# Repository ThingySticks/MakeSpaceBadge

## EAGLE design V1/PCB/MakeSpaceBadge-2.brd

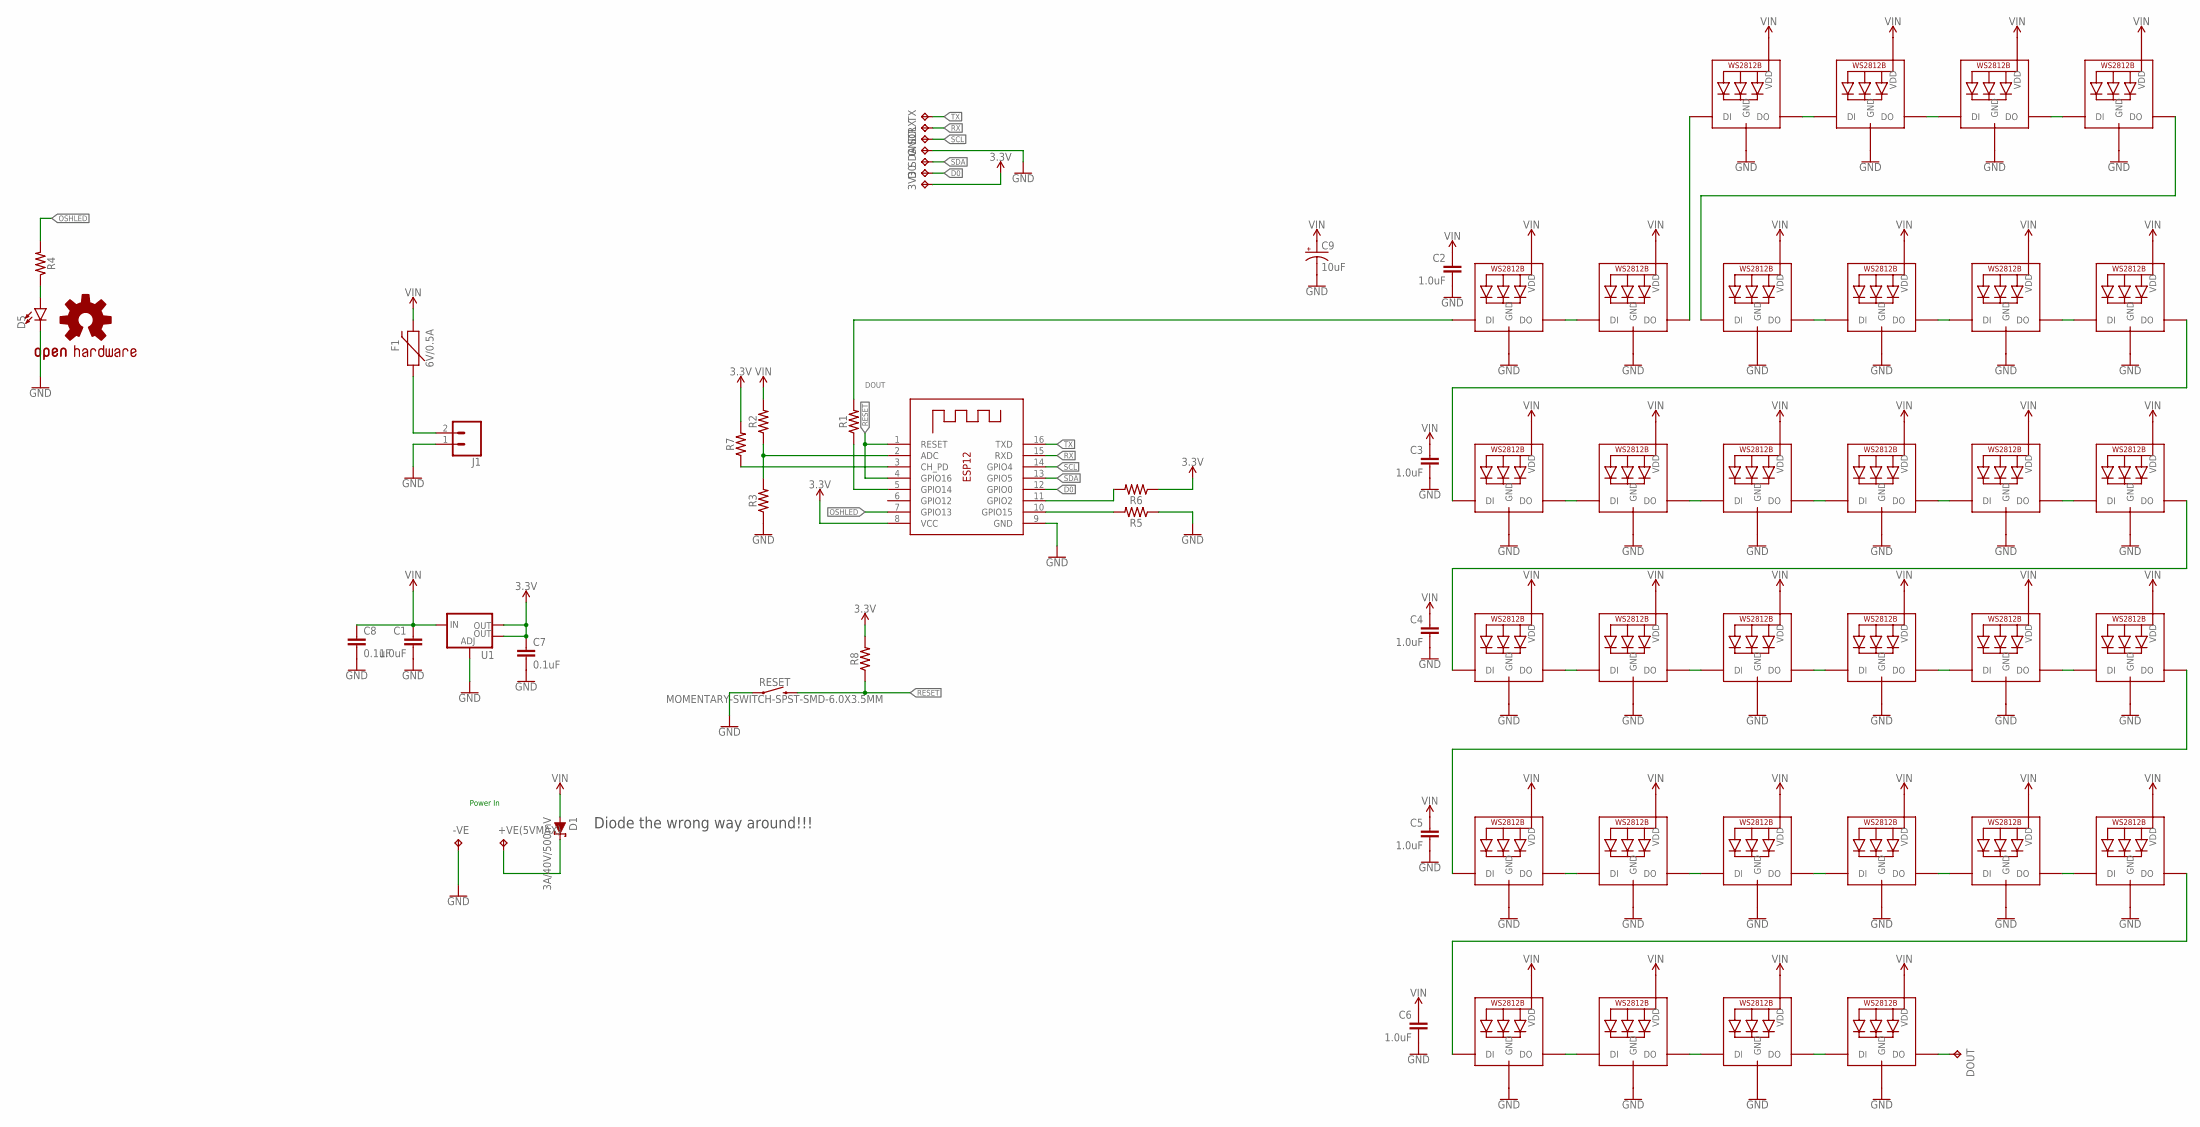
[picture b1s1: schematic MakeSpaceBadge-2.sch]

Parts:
3V3: TPTP20R; TP20R
+VE(5VMAX): TPTP20SQ; TP20SQ
-VE: TPTP20SQ; TP20SQ
C1, C2, C3, C4, C5, C6: 1.0uF; 0805
C7, C8: 0.1uF; 0805
C9: 10uF; EIA3216
D0: TPTP20R; TP20R
D1: 3A/40V/500mV; SMA-DIODE
D5: LED1206-BOTTOM; LED-1206-BOTTOM
DOUT: TPTP20R; TP20R
F1: 6V/0.5A; 1206
GND: TPTP20R; TP20R
J1: CONN_02-JST-2MM-SMT; JST-2-SMD
LED1, LED3, LED4, LED5, LED6, LED7, LED8, LED9, LED10, LED11, LED12, LED13, LED14, LED15, LED17, LED18, LED19, LED20, LED21, LED22, LED23, LED24, LED25, LED26, LED27, LED28, LED29, LED30, LED31, LED32: WS2812BBIGPADS; WS2812B-BIGPADS
LED2, LED16: WS2812B5050; WS2812B
LOGO1: OSHW-LOGOL; OSHW-LOGO-L
R1, R2, R3, R4, R5, R6, R7, R8: 0805
RESET: MOMENTARY-SWITCH-SPST-SMD-6.0X3.5MM; TACTILE_SWITCH_SMD_6.0X3.5MM
RX: TPTP20R; TP20R
SCL: TPTP20R; TP20R
SDA: TPTP20R; TP20R
TX: TPTP20R; TP20R
U1: V_REG_LM1117SOT223; SOT223
X1: ESP-12

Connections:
3.3V: 3V3.TP, C7.1, R6.1, R7.2, R8.2, U1.2 (OUT), U1.4 (OUT), X1.8 (VCC)
D0: D0.TP, X1.12 (GPIO0)
DOUT: LED1.4-DIN (DI), R1.2
GND: -VE.TP, C1.2, C2.2, C3.2, C4.2, C5.2, C6.2, C7.2, C8.2, C9.-, D5.C, GND.TP, J1.1 (2), LED1.3-GND (GND), LED2.3-GND (GND), LED3.3-GND (GND), LED4.3-GND (GND), LED5.3-GND (GND), LED6.3-GND (GND), LED7.3-GND (GND), LED8.3-GND (GND), LED9.3-GND (GND), LED10.3-GND (GND), LED11.3-GND (GND), LED12.3-GND (GND), LED13.3-GND (GND), LED14.3-GND (GND), LED15.3-GND (GND), LED16.3-GND (GND), LED17.3-GND (GND), LED18.3-GND (GND), LED19.3-GND (GND), LED20.3-GND (GND), LED21.3-GND (GND), LED22.3-GND (GND), LED23.3-GND (GND), LED24.3-GND (GND), LED25.3-GND (GND), LED26.3-GND (GND), LED27.3-GND (GND), LED28.3-GND (GND), LED29.3-GND (GND), LED30.3-GND (GND), LED31.3-GND (GND), LED32.3-GND (GND), R3.1, R5.1, RESET.1, U1.1 (ADJ), X1.9 (GND)
unnamed: R1.1, X1.5 (GPIO14)
unnamed: LED2.2-DOUT (DO), LED24.4-DIN (DI)
unnamed: LED1.2-DOUT (DO), LED2.4-DIN (DI)
unnamed: LED3.2-DOUT (DO), LED4.4-DIN (DI)
unnamed: LED4.2-DOUT (DO), LED5.4-DIN (DI)
unnamed: LED5.2-DOUT (DO), LED6.4-DIN (DI)
unnamed: LED6.2-DOUT (DO), LED7.4-DIN (DI)
unnamed: LED7.2-DOUT (DO), LED8.4-DIN (DI)
unnamed: LED8.2-DOUT (DO), LED9.4-DIN (DI)
unnamed: LED9.2-DOUT (DO), LED10.4-DIN (DI)
unnamed: LED10.2-DOUT (DO), LED11.4-DIN (DI)
unnamed: LED11.2-DOUT (DO), LED12.4-DIN (DI)
unnamed: LED12.2-DOUT (DO), LED13.4-DIN (DI)
unnamed: LED13.2-DOUT (DO), LED14.4-DIN (DI)
unnamed: LED14.2-DOUT (DO), LED15.4-DIN (DI)
unnamed: LED15.2-DOUT (DO), LED16.4-DIN (DI)
unnamed: LED16.2-DOUT (DO), LED17.4-DIN (DI)
unnamed: LED17.2-DOUT (DO), LED18.4-DIN (DI)
unnamed: LED18.2-DOUT (DO), LED19.4-DIN (DI)
unnamed: LED19.2-DOUT (DO), LED20.4-DIN (DI)
unnamed: LED20.2-DOUT (DO), LED21.4-DIN (DI)
unnamed: LED3.4-DIN (DI), LED32.2-DOUT (DO)
unnamed: LED23.4-DIN (DI), LED24.2-DOUT (DO)
unnamed: LED22.4-DIN (DI), LED23.2-DOUT (DO)
unnamed: R2.1, R3.2, X1.2 (ADC)
unnamed: D5.A, R4.1
unnamed: R5.2, X1.10 (GPIO15)
unnamed: F1.1, J1.2 (1)
unnamed: R6.2, X1.11 (GPIO2)
unnamed: DOUT.TP, LED31.2-DOUT (DO)
unnamed: +VE(5VMAX).TP, D1.C
unnamed: R7.1, X1.3 (CH_PD)
unnamed: LED22.2-DOUT (DO), LED32.4-DIN (DI)
unnamed: LED21.2-DOUT (DO), LED25.4-DIN (DI)
unnamed: LED25.2-DOUT (DO), LED26.4-DIN (DI)
unnamed: LED26.2-DOUT (DO), LED27.4-DIN (DI)
unnamed: LED28.2-DOUT (DO), LED29.4-DIN (DI)
unnamed: LED29.2-DOUT (DO), LED30.4-DIN (DI)
unnamed: LED30.2-DOUT (DO), LED31.4-DIN (DI)
unnamed: LED27.2-DOUT (DO), LED28.4-DIN (DI)
OSHLED: R4.2, X1.7 (GPIO13)
RESET: R8.1, RESET.2, X1.1 (RESET), X1.4 (GPIO16)
RX: RX.TP, X1.15 (RXD)
SCL: SCL.TP, X1.14 (GPIO4)
SDA: SDA.TP, X1.13 (GPIO5)
TX: TX.TP, X1.16 (TXD)
VIN: C1.1, C2.1, C3.1, C4.1, C5.1, C6.1, C8.1, C9.+, D1.A, F1.2, LED1.1-VDD (VDD), LED2.1-VDD (VDD), LED3.1-VDD (VDD), LED4.1-VDD (VDD), LED5.1-VDD (VDD), LED6.1-VDD (VDD), LED7.1-VDD (VDD), LED8.1-VDD (VDD), LED9.1-VDD (VDD), LED10.1-VDD (VDD), LED11.1-VDD (VDD), LED12.1-VDD (VDD), LED13.1-VDD (VDD), LED14.1-VDD (VDD), LED15.1-VDD (VDD), LED16.1-VDD (VDD), LED17.1-VDD (VDD), LED18.1-VDD (VDD), LED19.1-VDD (VDD), LED20.1-VDD (VDD), LED21.1-VDD (VDD), LED22.1-VDD (VDD), LED23.1-VDD (VDD), LED24.1-VDD (VDD), LED25.1-VDD (VDD), LED26.1-VDD (VDD), LED27.1-VDD (VDD), LED28.1-VDD (VDD), LED29.1-VDD (VDD), LED30.1-VDD (VDD), LED31.1-VDD (VDD), LED32.1-VDD (VDD), R2.2, U1.3 (IN)

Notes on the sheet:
Power In
Diode the wrong way around!!!

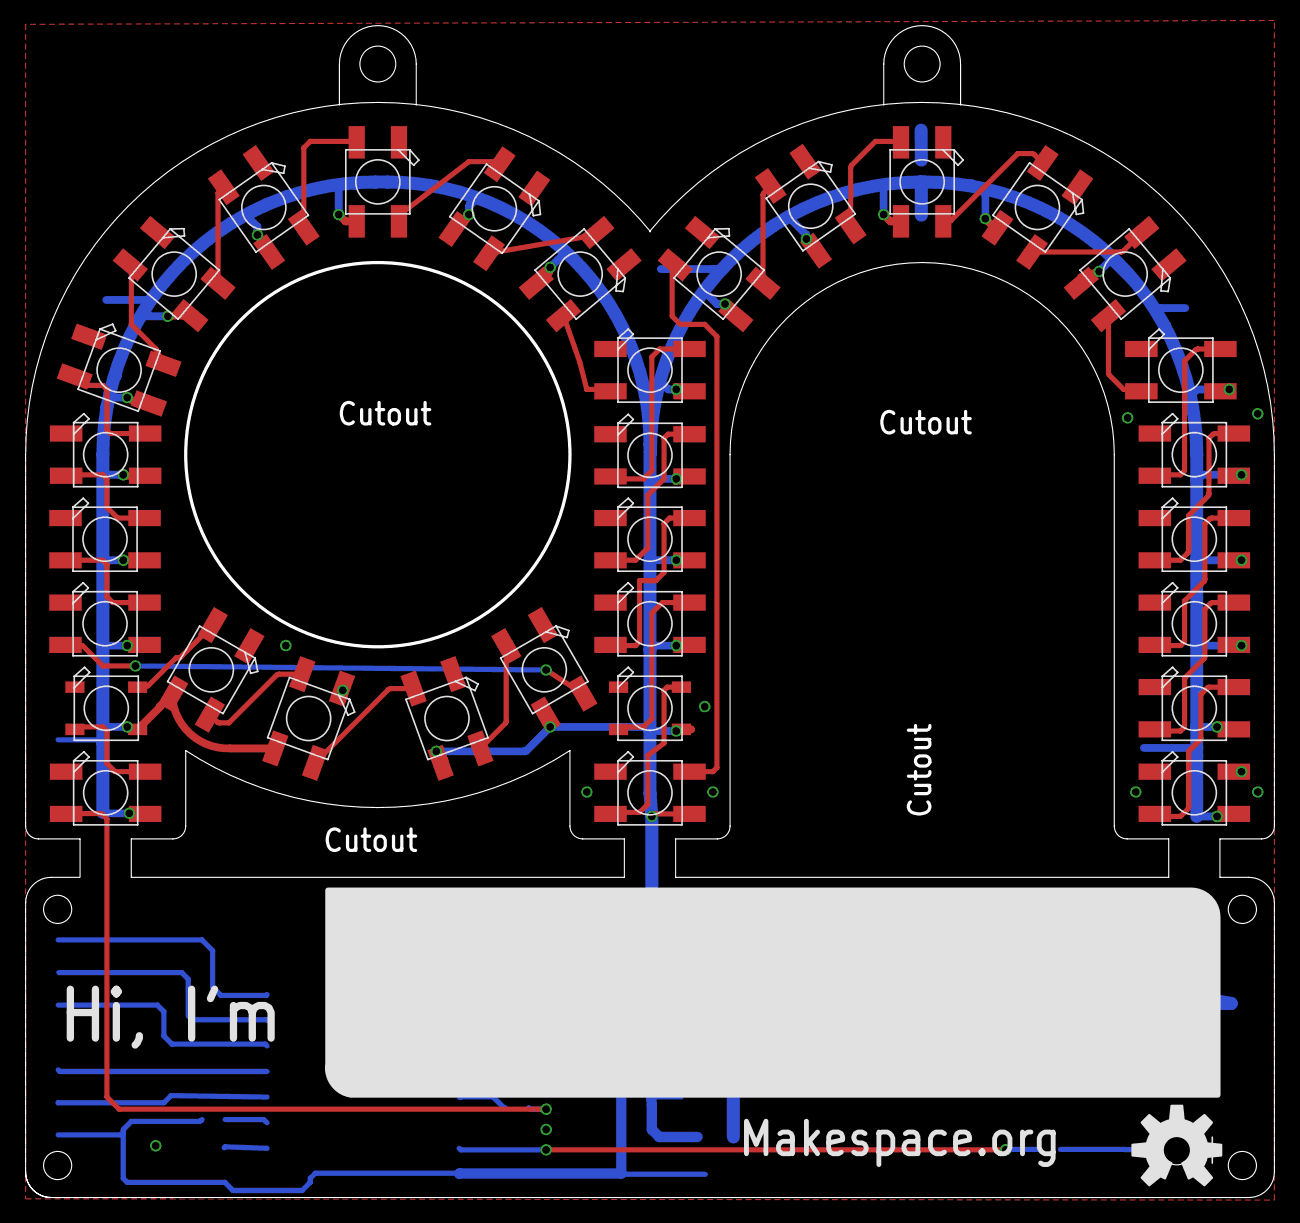
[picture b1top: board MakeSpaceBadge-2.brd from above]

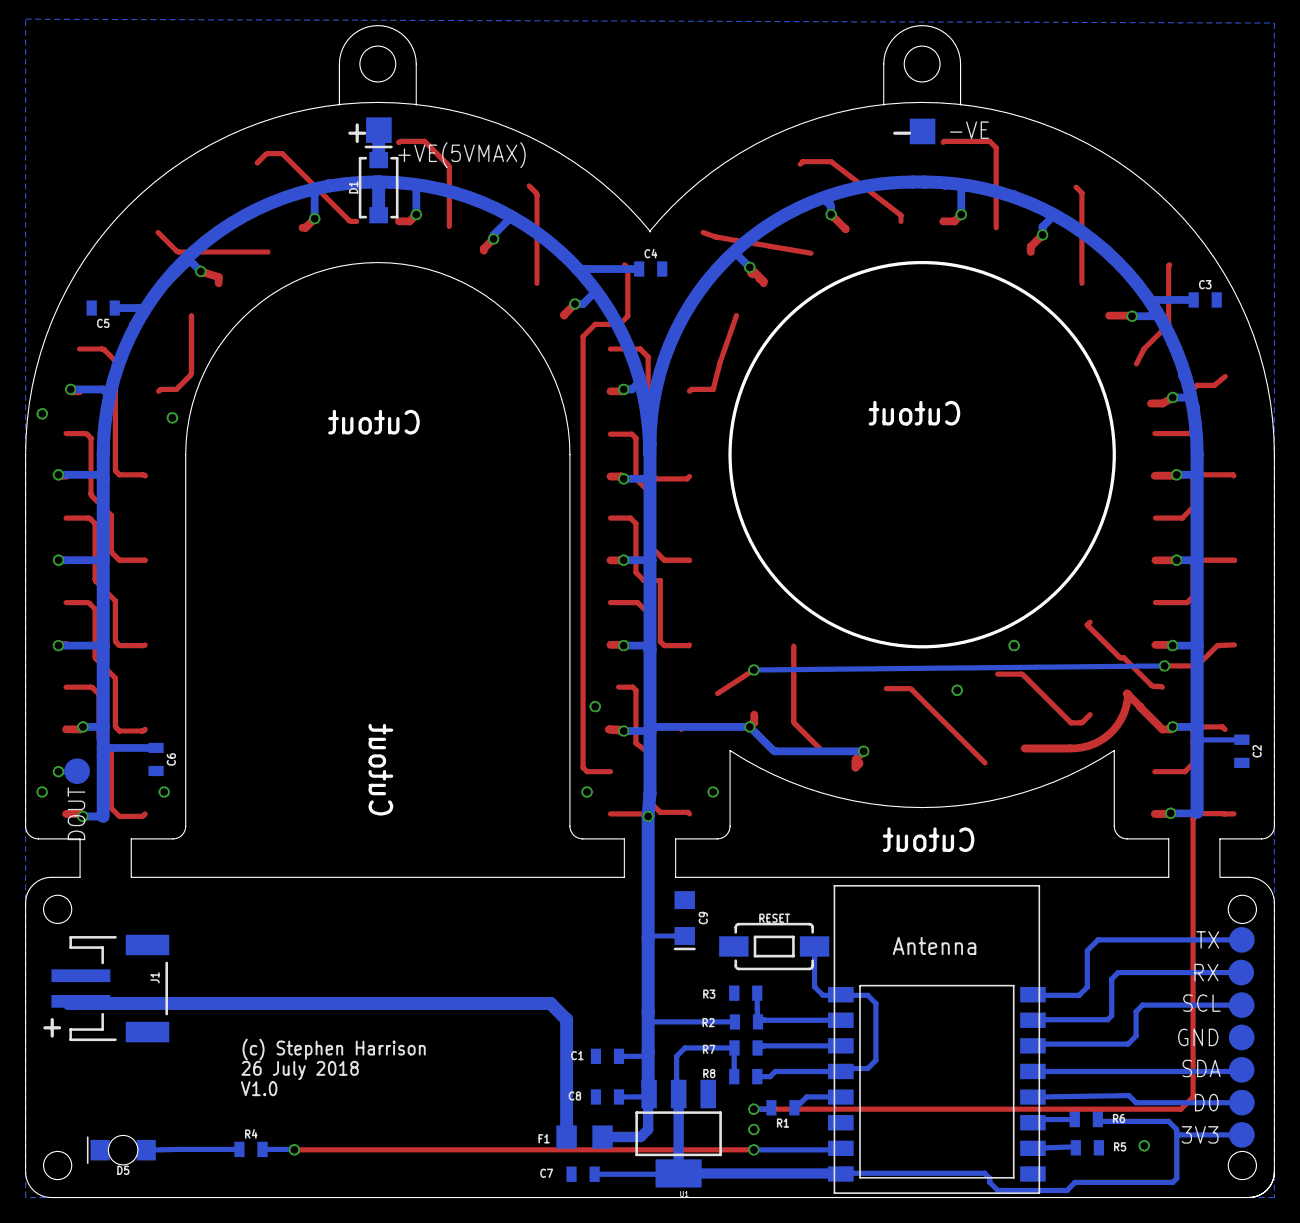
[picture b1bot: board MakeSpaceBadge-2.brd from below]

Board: 2 copper layers, 97.2 x 91.2 mm, 67 parts (34 on the bottom side), 51 nets.

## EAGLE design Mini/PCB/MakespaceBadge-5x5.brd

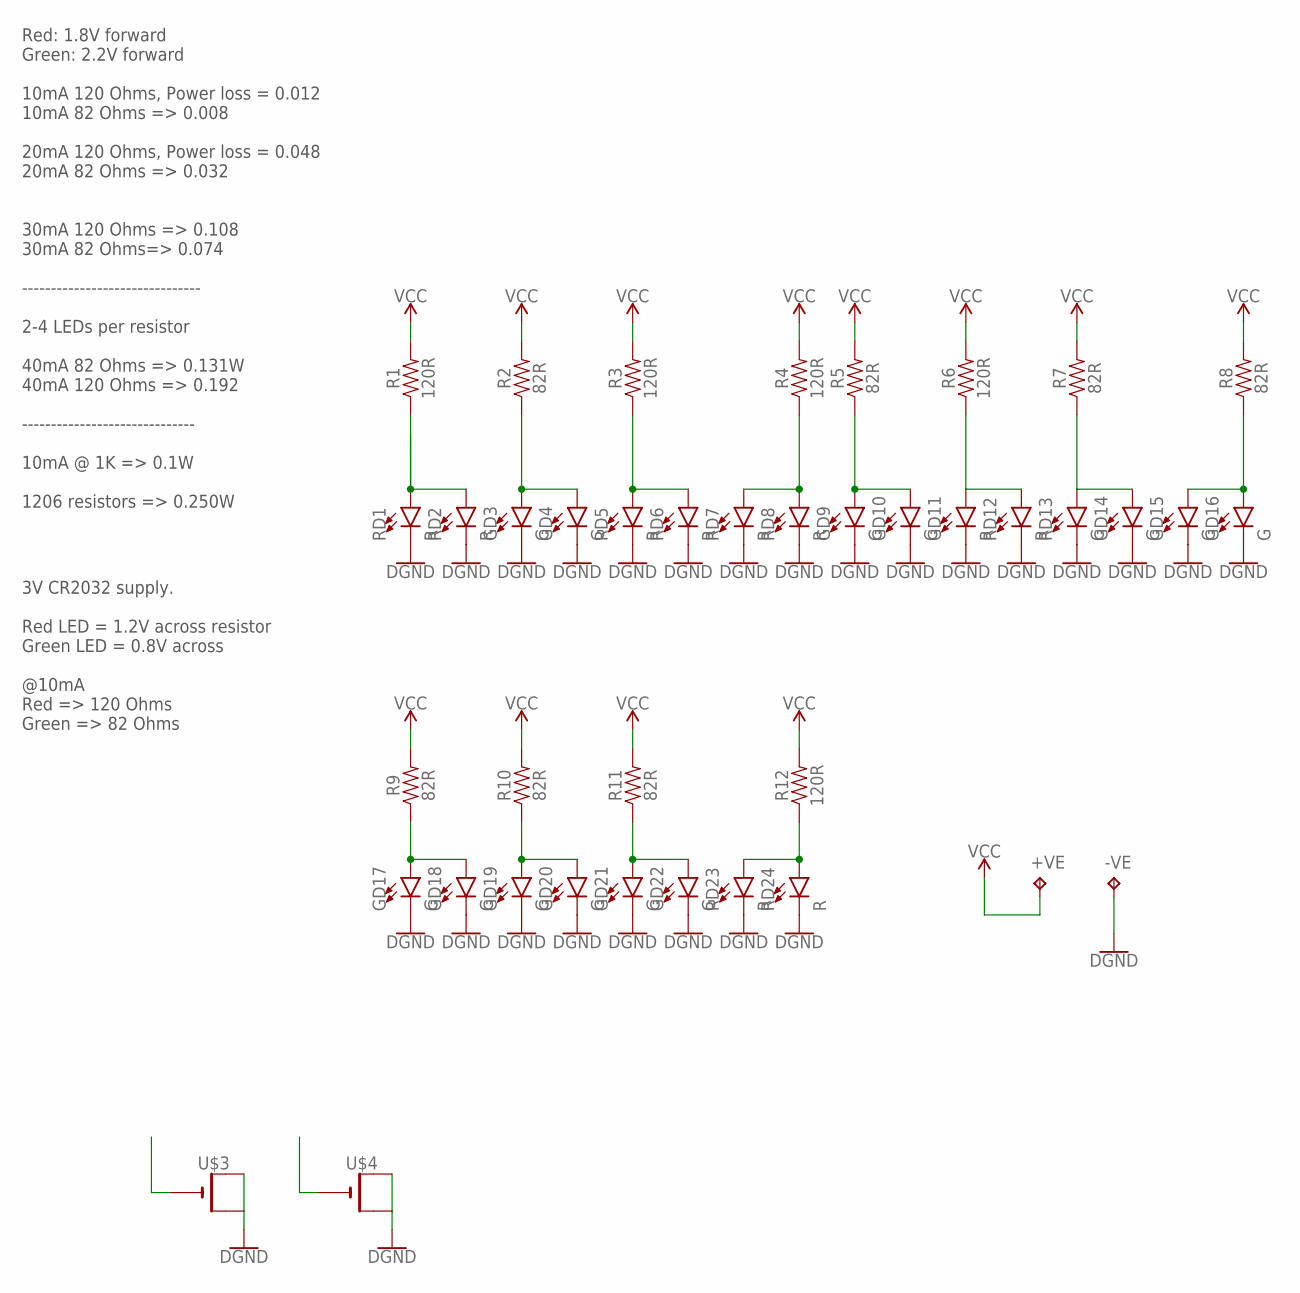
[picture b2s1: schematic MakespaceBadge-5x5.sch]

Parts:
+VE: TPTP20SQ; TP20SQ
-VE: TPTP20SQ; TP20SQ
GD3, GD4, GD9, GD10, GD14, GD15, GD16, GD17, GD18, GD19, GD20, GD21, GD22: G; LED_3MM
GD11: R; LED_3MM
R1, R3, R4, R6, R12: 120R; 1206
R2, R5, R7, R8, R9, R10, R11: 82R; 1206
RD1, RD2, RD5, RD6, RD7, RD8, RD12, RD23, RD24: R; LED_3MM
RD13: G; LED_3MM
U$3, U$4: CR1220SMT; CR1220-SMD

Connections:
GND: -VE.TP, GD3.K (C), GD4.K (C), GD9.K (C), GD10.K (C), GD11.K (C), GD14.K (C), GD15.K (C), GD16.K (C), GD17.K (C), GD18.K (C), GD19.K (C), GD20.K (C), GD21.K (C), GD22.K (C), RD1.K (C), RD2.K (C), RD5.K (C), RD6.K (C), RD7.K (C), RD8.K (C), RD12.K (C), RD13.K (C), RD23.K (C), RD24.K (C), U$3.+$1 (+), U$3.+$2 (+1), U$4.+$1 (+), U$4.+$2 (+1)
unnamed: R1.1, RD1.A, RD2.A
unnamed: GD3.A, GD4.A, R2.1
unnamed: R4.1, RD7.A, RD8.A
unnamed: GD9.A, GD10.A, R5.1
unnamed: GD14.A, R7.1, RD13.A
unnamed: GD21.A, GD22.A, R11.1
unnamed: R12.1, RD23.A, RD24.A
unnamed: R3.1, RD5.A, RD6.A
unnamed: GD11.A, R6.1, RD12.A
unnamed: GD15.A, GD16.A, R8.1
unnamed: GD17.A, GD18.A, R9.1
unnamed: GD19.A, GD20.A, R10.1
VCC: +VE.TP, R1.2, R2.2, R3.2, R4.2, R5.2, R6.2, R7.2, R8.2, R9.2, R10.2, R11.2, R12.2

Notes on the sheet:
Red: 1.8V forward Green: 2.2V forward 10mA 120 Ohms, Power loss = 0.012 10mA 82 Ohms => 0.008 20mA 120 Ohms, Power loss = 0.048 20mA 82 Ohms => 0.032 30mA 120 Ohms => 0.108 30mA 82 Ohms=> 0.074 ------------------------------- 2-4 LEDs per resistor 40mA 82 Ohms => 0.131W 40mA 120 Ohms => 0.192 -----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
3V CR2032 supply. Red LED = 1.2V across resistor Green LED = 0.8V across @10mA Red => 120 Ohms Green => 82 Ohms

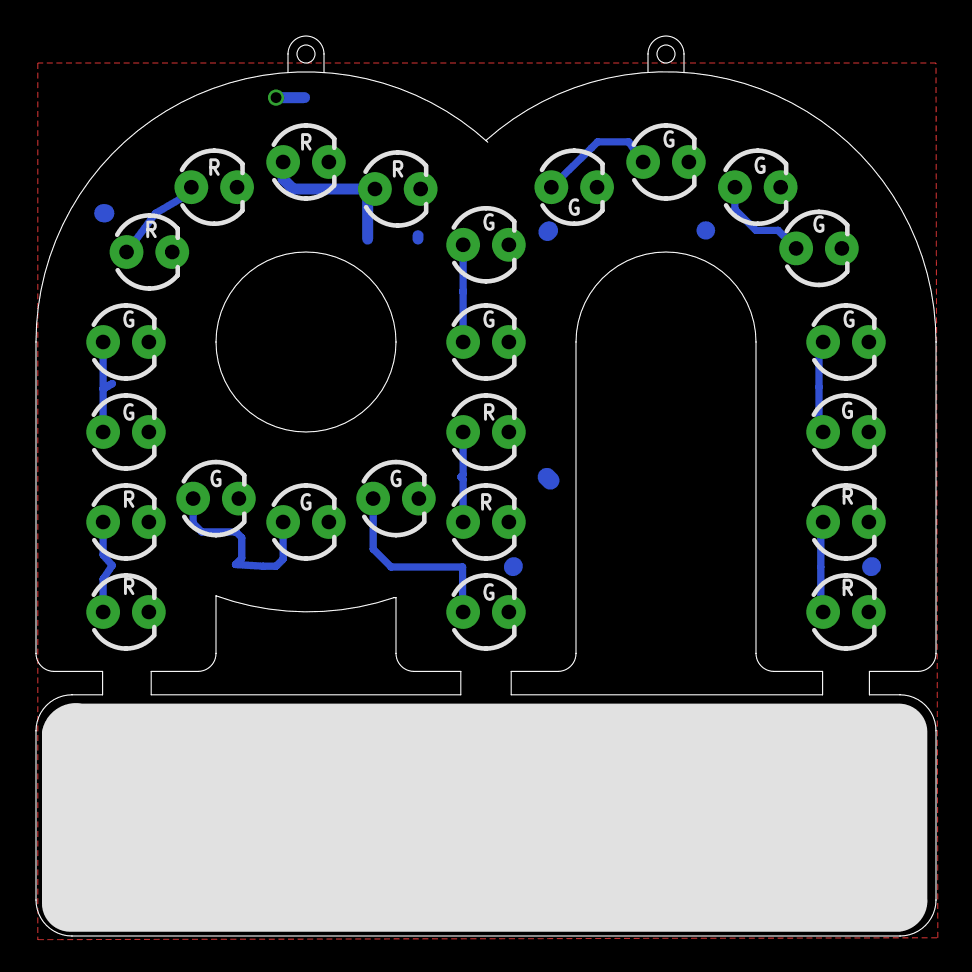
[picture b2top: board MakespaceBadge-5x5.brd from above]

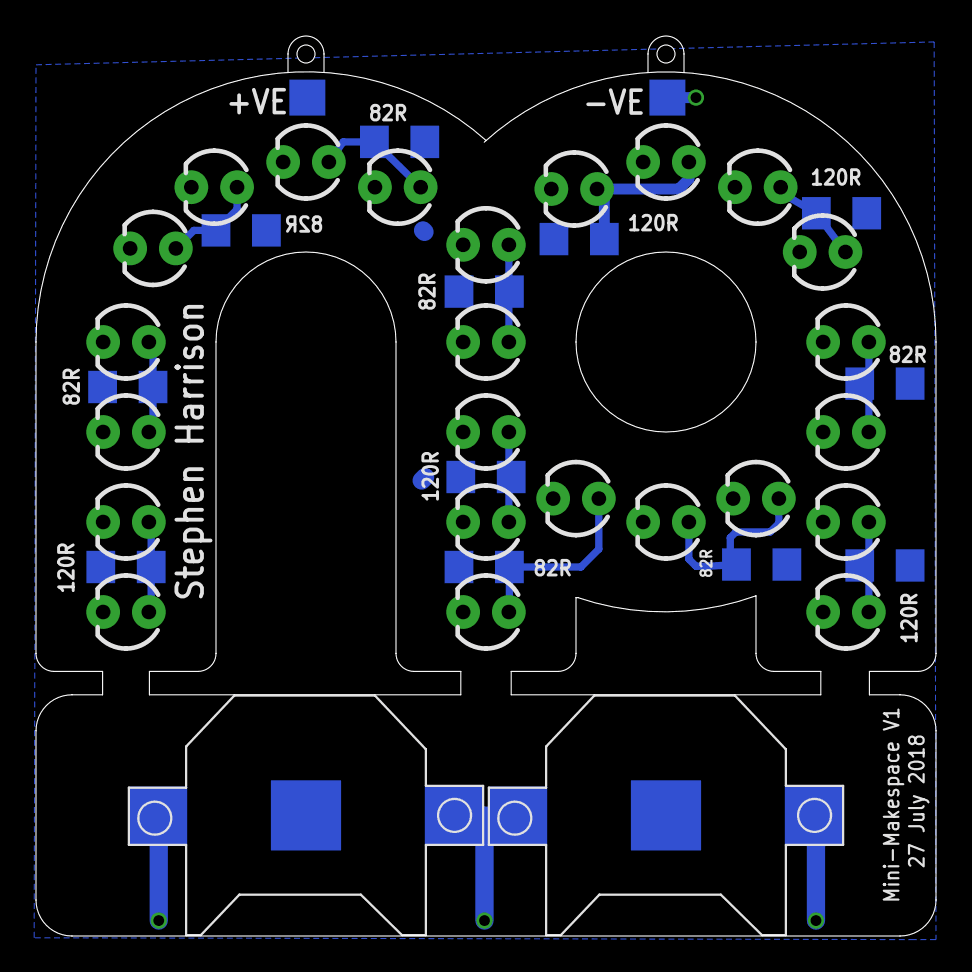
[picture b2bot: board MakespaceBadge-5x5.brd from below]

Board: 2 copper layers, 50.0 x 50.0 mm, 40 parts (16 on the bottom side), 14 nets.

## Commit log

2018-07-26 Initial attempt, 70mm sized.
2018-07-26 Version 1 (better use of 10x10 board) as sent to DirtyPCBs
2018-07-28 Added 5cm x 5cm mini badge with 3mm LEDs - as sent to DirtyPCBs.com
2018-08-11 Added notes.
    Added mini case to hold battery/protect electronics.
    Added firmware to drive leds.

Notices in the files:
parts and their libraries:
SparkFun-LED: Licensing: Creative Commons ShareAlike 4.0 International - https://creativecommons.org/licenses/by-sa/4.0
